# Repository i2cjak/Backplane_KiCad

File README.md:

# Backplane KiCad

This is Backplane's public KiCad fork, based on the stable KiCad 10.0.6 release.
It carries focused IPC backports for use alongside the
[Backplane app](https://github.com/i2cjak/Backplane). See
[the IPC build contract](BACKPLANE_IPC.md) for the current scope and build details.

The original KiCad licenses, attribution, and upstream documentation are retained below.

## KiCad

For specific documentation about [building KiCad](https://dev-docs.kicad.org/en/build/), policies
and guidelines, and source code documentation see the
[Developer Documentation](https://dev-docs.kicad.org) website.

You may also take a look into the [Wiki](https://gitlab.com/kicad/code/kicad/-/wikis/home),
the [contribution guide](https://dev-docs.kicad.org/en/contribute/).

For general information about KiCad and information about contributing to the documentation and
libraries, see our [Website](https://kicad.org/) and our [Forum](https://forum.kicad.info/).

## Build state

KiCad uses a host of CI resources.

GitLab CI pipeline status can be viewed for Linux and Windows builds of the latest commits.

## Release status

## Files
* [AUTHORS.txt](AUTHORS.txt) - The authors, contributors, document writers and translators list
* [CMakeLists.txt](CMakeLists.txt) - Main CMAKE build tool script
* [copyright.h](copyright.h) - A very short copy of the GNU General Public License to be included in new source files
* [Doxyfile](Doxyfile) - Doxygen config file for KiCad
* [INSTALL.txt](INSTALL.txt) - The release (binary) installation instructions
* [uncrustify.cfg](uncrustify.cfg) - Uncrustify config file for uncrustify sources formatting tool
* [_clang-format](_clang-format) - clang config file for clang-format sources formatting tool

## Subdirectories

* [3d-viewer](3d-viewer)         - Sourcecode of the 3D viewer
* [bitmap2component](bitmap2component)  - Sourcecode of the bitmap to PCB artwork converter
* [cmake](cmake)      - Modules for the CMAKE build tool
* [common](common)            - Sourcecode of the common library
* [cvpcb](cvpcb)             - Sourcecode of the CvPCB tool
* [demos](demos)             - Some demo examples
* [doxygen](doxygen)     - Configuration for generating pretty doxygen manual of the codebase
* [eeschema](eeschema)          - Sourcecode of the schematic editor
* [gerbview](gerbview)          - Sourcecode of the gerber viewer
* [include](include)           - Interfaces to the common library
* [kicad](kicad)             - Sourcecode of the project manager
* [libs](libs)           - Sourcecode of KiCad utilities (geometry and others)
* [pagelayout_editor](pagelayout_editor) - Sourcecode of the pagelayout editor
* [patches](patches)           - Collection of patches for external dependencies
* [pcbnew](pcbnew)           - Sourcecode of the printed circuit board editor
* [plugins](plugins)           - Sourcecode for the 3D viewer plugins
* [qa](qa)                - Unit testing framework for KiCad
* [resources](resources)         - Packaging resources such as bitmaps and operating system specific files
    - [bitmaps_png](resources/bitmaps_png)       - Menu and program icons
    - [project_template](resources/project_template)          - Project template
* [scripting](scripting)         - Python integration for KiCad
* [thirdparty](thirdparty)           - Sourcecode of external libraries used in KiCad but not written by the KiCad team
* [tools](tools)             - Helpers for developing, testing and building
* [translation](translation) - Translation data files (managed through [Weblate](https://hosted.weblate.org/projects/kicad/master-source/) for most languages)
* [utils](utils)             - Small utils for KiCad, e.g. IDF, STEP, and OGL tools and converters

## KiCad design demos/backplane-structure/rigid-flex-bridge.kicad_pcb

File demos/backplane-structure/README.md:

# Board construction examples

These boards use stock KiCad 10.0.6 native artwork plus adjacent
`.kicad_pcb.backplane.json` construction companions. Keep each pair together.
All coordinates in the companion are native nanometres unless a field explicitly
uses `_mm` or degrees.

- **reinforced-flex**: two copper layers on a 0.15 mm flex substrate, top coverlay,
  bottom 0.30 mm FR4 terminal stiffener with 0.025 mm adhesive, and a 90 degree fold.
- **rigid-flex-bridge**: two 1.6 mm rigid islands joined by a 0.15 mm flex bridge.
  In1.Cu and In2.Cu remain continuous at the same physical height through all
  regions. The outer copper exists only on the rigid islands.
- **two-bend-u-fold**: the bridge receives sequential 90 degree bends at x=55 and
  x=70 mm, returning the moving island to a parallel plane above the fixed island.
  It also carries SOIC-8 and 0805 SMD package fixtures on both islands for model
  seating/orientation checks. These additional SMD pads have no assigned nets.

All three examples have two routed nets and four drilled through-hole terminals.
Each terminal references the stock KiCad 1×1 vertical 2.54 mm pin-header STEP
model through `KICAD10_3DMODEL_DIR`; install the KiCad 3D model library to view them.
The bend starts at x=55 mm; the positive-X side moves with a 2 mm inner radius.
The reinforcement was explicitly placed at the terminal area; there is no
automatic mechanical stiffener-placement solver.

In Board Setup, use **Rigid-Flex Structure** to edit the region, regional stack,
stiffener, coverlay and bend definitions. The regional stack layer editor controls
material thickness and physical Z offsets independently of native copper identity.

Local regression commands (use a freshly built fork executable):

```sh
kicad-cli pcb structure rigid-flex-bridge.kicad_pcb
kicad-cli pcb export gerbers rigid-flex-bridge.kicad_pcb --output fabrication/
kicad-cli pcb export drill rigid-flex-bridge.kicad_pcb --output fabrication/
kicad-cli pcb export step rigid-flex-bridge.kicad_pcb --no-components --output flat.step
```

Construction Gerbers describe positive material areas, with clear holes/openings.
Bend-area Gerbers are reference drawings. They are not copper, milling, or material
layers. `board-construction.json` identifies each output and carries the material,
adhesive, thickness and bend specification. Native copper and fabrication
artwork always remain in the flat developed state.

The nine native/project/companion files are immutable migration fixtures from
`1747f64599`. Generate new examples outside this directory using KiCad Python:

```sh
python3 scripts/backplane-create-structure-exemplars.py --output /tmp/new-structure-examples
python3 scripts/backplane-populate-smd-exemplar.py /tmp/new-structure-examples/two-bend-u-fold.kicad_pcb
```

Run the independent local regression using an environment containing
`gerbonara` and `cadquery-ocp`:

```sh
python scripts/backplane-structure-stock-check.py /path/to/fork/kicad-cli \
  --stock-cli /usr/bin/kicad-cli --output /tmp/structure-regression --folded
```

See the repository research specification for the intended broader feature set.
These are engineering test fixtures, not fabrication-qualified product designs.

To render the actual exported construction solids locally, install `cadquery-ocp`
in your Python environment and use Blender:

```sh
python scripts/backplane-tessellate-step.py folded.step /tmp/folded-mesh.json
blender --background --python scripts/backplane-render-construction.py -- \
  /tmp/folded-mesh.json /tmp/folded.png
```

The renderer also saves a `.blend` scene beside the PNG. Add `--square` for a 1600 × 1600 image. Use `--underside` to
inspect a bottom stiffener. Colors are presentation choices; use the construction
manifest to identify actual materials and thicknesses.

## Master migration

Opening these v1 companions on master retains structure. Saving a copied board
writes current native master fields and a v2 companion containing only extensions.
Do not resave the authoritative fixtures. Run
`scripts/backplane-structure-migration-regression.py /path/to/kicad-cli` for the
headless migration gate. No native master validation has been run for this port.
For stock KiCad 10, use `project downgrade --target 10.0` on a disposable copy.
See [KiCad 10 export](../../BACKPLANE_RIGID_FLEX_SPEC.md#kicad-10-export) for
what stock sees and what downgrade removes or approximates.

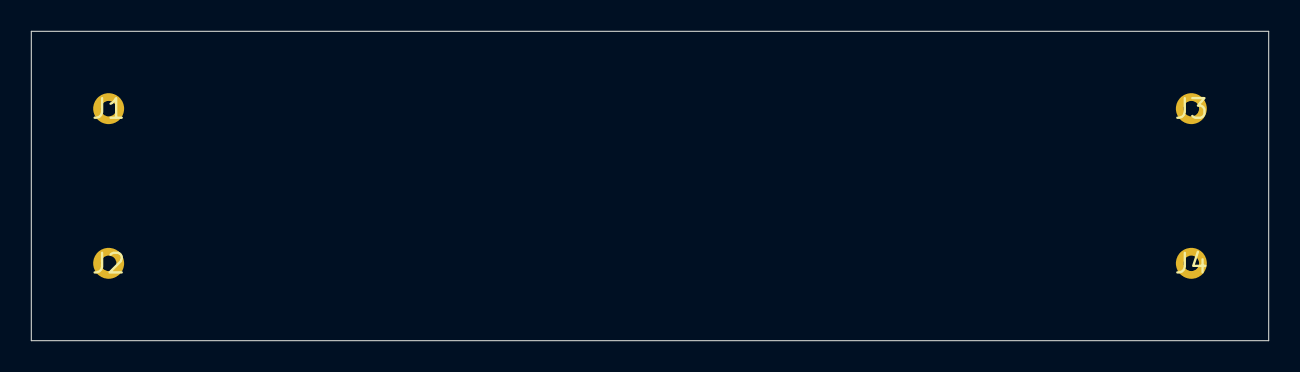
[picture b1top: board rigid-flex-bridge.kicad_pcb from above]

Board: 4 copper layers, 80.0 x 20.0 mm, 4 parts (0 on the bottom side), 2 nets.

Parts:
J1, J2, J3, J4: Test terminal

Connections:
SIGNAL_1: J1.1, J3.1
SIGNAL_2: J2.1, J4.1
